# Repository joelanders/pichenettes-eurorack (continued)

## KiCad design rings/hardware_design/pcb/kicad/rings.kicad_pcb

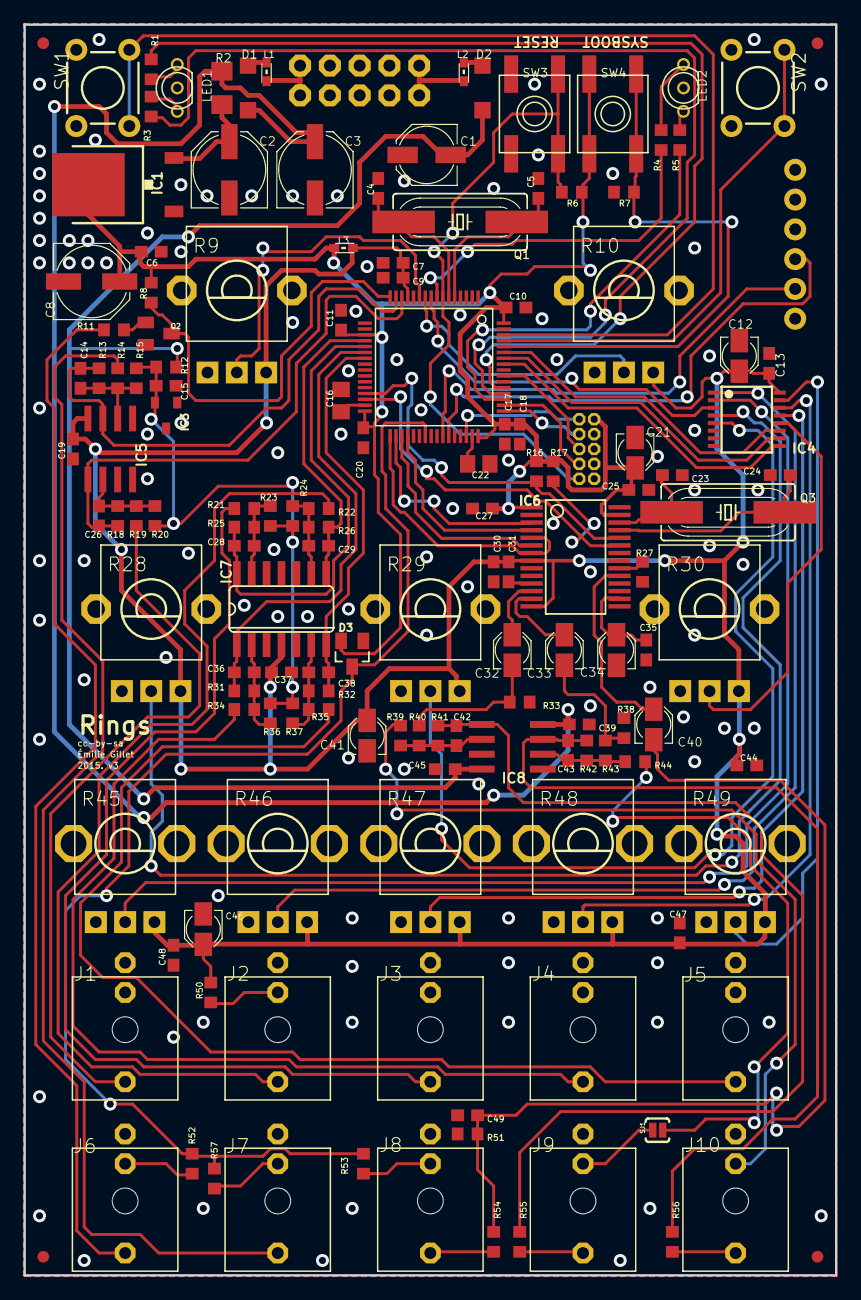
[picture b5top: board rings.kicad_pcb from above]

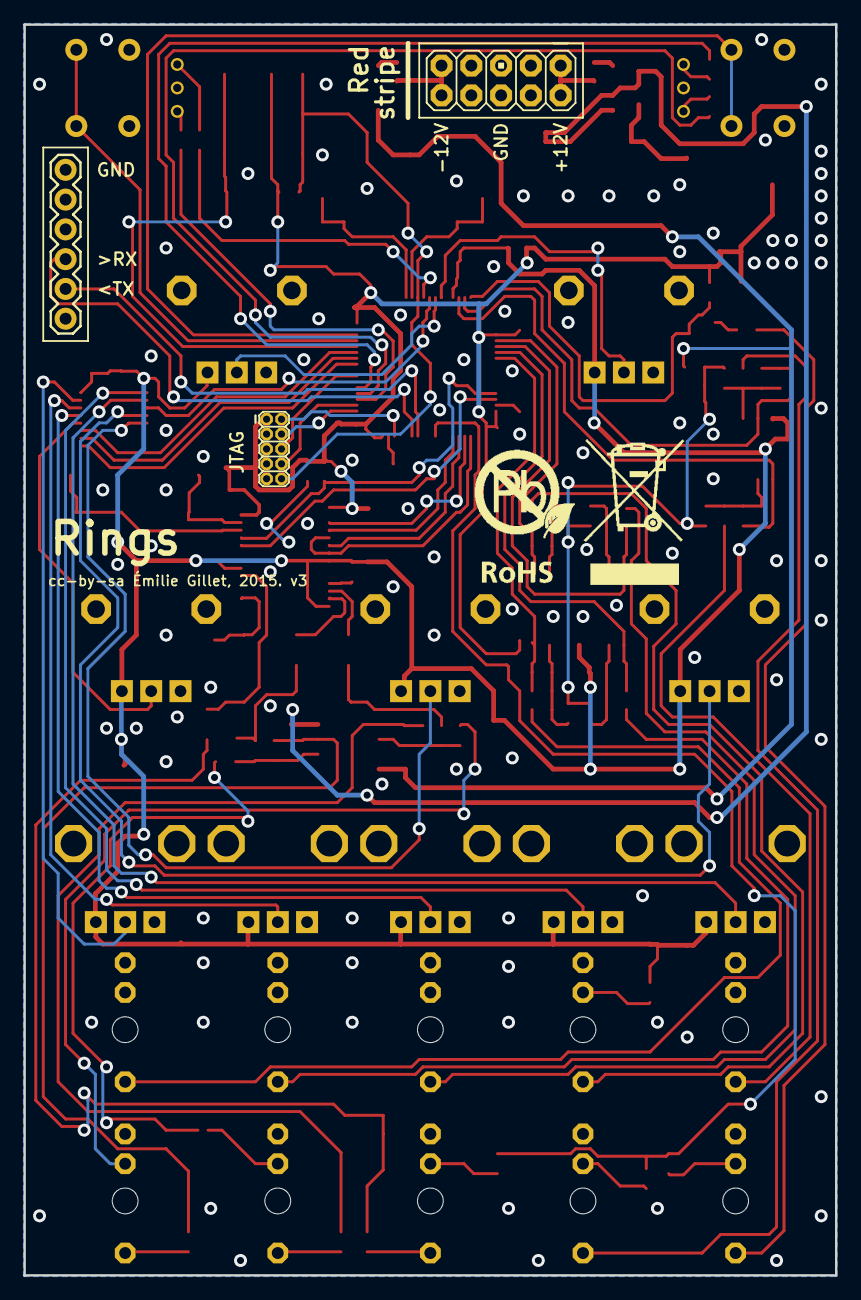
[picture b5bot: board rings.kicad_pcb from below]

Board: 2 copper layers, 69.2 x 106.7 mm, 148 parts (4 on the bottom side), 99 nets.

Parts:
C1: 22u; PANASONIC_C
C2, C3, C8: 47u; PANASONIC_D
C4, C5, C23, C24, C42, C43: 18p; C0603
C6, C9, C10, C11, C13, C15, C17, C19, C20, C25, C27, C31, C35, C37, C39, C44, C45, C47, C48: 100n; C0603
C7, C18, C30: 1u; C0603
C12, C21, C32, C33, C34, C40, C41, C46: 10u; PANASONIC_A
C14, C29: 2.2n; C0603
C16, C22: 2.2u; C0805
C26, C28, C36, C38: 10n; C0603
C49: 220p; C0603
D1, D2: 1N5819HW; SOD123
D3: BAT54S; SOT23
F1, F2, F3, F4: FIDUCIAL1X2; FIDUCIAL-1X2
IC1: LM1117-3.3; TO252
IC2: STM32F405RGT6; TQFP-10X10-64
IC3: LM4040B10; DBZ_R-PDSO-G3
IC4: 4051PW; TSSOP16
IC5: MCP6002; SO08
IC6: WM8731; SSOP28
IC7: MCP6004; SO14
IC8: TL072; SO08
J1, J2, J3, J4, J5, J6, J7, J8, J9, J10: PJ301_THONKICONN6; WQP_PJ_301M6
JP1: M05X2MINIJTAG; 2X5-1.27
JP2: 1X06
JP3: M05X2PTH; AVR_ICSP
L1, L2, L3: 0603
LED1, LED2: WP115VEGW; LED-BICOLOR-THROUGHHOLE
Q1: 8MHz; HC49UP
Q2: MMBT3904; SOT23-BEC
Q3: 12.288MHz; HC49UP
R1, R3, R4, R5: 180; R0603
R2: 4.7; R1206
R6, R7, R8: 10k; R0603
R9, R10, R28, R29, R30: 10kB; ALPS_POT_VERTICAL_PS
R11, R14, R19, R21, R22, R34, R35, R52: 100k; R0603
R12, R16, R17: 2.2k; R0603
R13, R33, R38, R39, R41, R42, R44: 47k; R0603
R15: 180k; R0603
R18, R25, R26, R31, R32: 20k; R0603
R20, R23, R24, R36, R37: 120k; R0603
R27, R54: 36k; R0603
R40, R43, R51: 6.8k; R0603
R45, R46, R47, R48, R49: 10kB; ALPS_POT_VERTICAL
R50: 3.3M; R0603
R53: 1M; R0603
R55, R56: 1.0k; R0603
R57: 470k; R0603
SJ1: SOLDERJUMPERNC2; SJ_2S-NOTRACE
SW1, SW2: TACTILE-PTH
SW3, SW4: EVQ-Q2
U$2: ROHS_BIG

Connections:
+3V3: C6.1, C8.+, C10.1, C11.1, C17.1, C18.1, C20.1, C21.+, C25.1, C27.1, D3.2, IC1.3, IC2.19, IC2.32, IC2.48, IC2.64, IC6.1, IC6.27, JP1.1, L3.1, R6.2, R8.2, R16.2, R17.2, SW4.B, SW4.B'
+3V3_A: C7.1, C9.1, C12.+, C13.1, C19.1, C30.1, C31.1, C37.1, C41.+, C44.1, C46.+, C47.1, C48.1, IC2.13, IC4.16, IC5.8, IC6.8, IC6.14, IC7.4, L3.2, R9.P$1, R10.P$1, R28.P$1, R29.P$1, R30.P$1, R45.P$1, R46.P$1, R47.P$1, R48.P$1, R49.P$1, R50.2
AREF_-10: C15.1, IC3.2, R12.2, R15.2, R20.2, R23.2, R24.2, R36.2, R37.2
AUX_OUT: C33.+, IC6.13
BOOT_FLASH: IC2.60, R7.2, SW4.A, SW4.A'
BRIGHTNESS_ATT: IC4.2, R45.P$2
BRIGHTNESS_CV: C26.2, IC2.14, IC5.1, R18.1
BRIGHTNESS_POT: IC4.4, R28.P$2
CV_NORMALIZATION: J7.P2, R57.2
DAMP_ATT: IC4.13, R47.P$2
DAMP_CV: C28.2, IC2.21, IC7.14, R25.1
DAMP_POT: IC4.5, R29.P$2
FM_CV: C29.2, IC2.20, IC7.8, R26.1
FREQUENCY_ATT: IC4.1, R46.P$2
FREQUENCY_POT: IC2.11, R9.P$2
GEOMETRY_ATT: IC4.14, R48.P$2
GEOMETRY_CV: C36.2, IC2.22, IC7.1, R31.1
GEOMETRY_POT: IC2.10, R10.P$2
GND: C1.+, C2.-, C3.-, C4.1, C5.1, C6.2, C7.2, C8.-, C9.2, C10.2, C11.2, C12.-, C13.2, C15.2, C16.2, C17.2, C18.2, C19.2, C20.2, C21.-, C22.2, C23.1, C24.1, C25.2, C27.2, C30.2, C31.2, C34.-, C35.2, C37.2, C39.2, C41.-, C44.2, C45.1, C46.-, C47.2, C48.2, C49.2, D3.1, IC1.1, IC2.12, IC2.18, IC2.26, IC2.28, IC2.63, IC3.1, IC4.6, IC4.7, IC4.8, IC5.3, IC5.4, IC5.5, IC6.11, IC6.15, IC6.21, IC6.22, IC6.28, IC7.3, IC7.5, IC7.10, IC7.11, IC7.12, IC8.3, IC8.5, J1.P1, J2.P1, J3.P1, J4.P1, J5.P1, J6.P1, J7.P1, J8.P1, J9.P1, J10.P1, JP1.3, JP1.5, JP1.9, JP2.1, JP3.3, JP3.4, JP3.5, JP3.6, JP3.7, JP3.8, LED1.2, LED2.2, Q2.E, R7.1, R9.P$3, R10.P$3, R27.2, R28.P$3, R29.P$3, R30.P$3, R33.1, R38.1, R45.P$3, R46.P$3, R47.P$3, R48.P$3, R49.P$3, R51.1, SW1.1, SW1.2, SW2.1, SW2.2, SW3.A, SW3.A'
I2C_SCL: IC2.29, IC6.24, R16.1
I2C_SDA: IC2.30, IC6.23, R17.1
I2S_LRCK: IC2.33, IC6.5, IC6.7
I2S_SCK: IC2.34, IC6.3
I2S_SIN: IC2.35, IC6.6
I2S_SOUT: IC2.36, IC6.4
IN_1: IC6.20, R27.1
IN_2: C40.+, IC6.19
JTCK: IC2.49, JP1.4
JTDI: IC2.50, JP1.8
JTDO: IC2.55, JP1.6
JTMS: IC2.46, JP1.2
MAIN_OUT: C32.+, IC6.12
MUXED_POTS: IC2.9, IC4.3
MUX_ADDR_0: IC2.59, IC4.11
MUX_ADDR_1: IC2.58, IC4.10
MUX_ADDR_2: IC2.57, IC4.9
unnamed: J1.P3, R19.2
unnamed: C26.1, IC5.2, R18.2, R19.1, R20.1
unnamed: J7.P3, R14.2
unnamed: J2.P3, R22.2
unnamed: C29.1, IC7.9, R22.1, R24.1, R26.2
unnamed: J4.P3, R34.2
unnamed: C5.2, IC2.5, Q1.2
unnamed: C4.2, IC2.6, Q1.1
unnamed: J6.P3, R11.1
unnamed: J3.P3, R21.2
unnamed: C28.1, IC7.13, R21.1, R23.1, R25.2
unnamed: LED1.3, R1.2
unnamed: C22.1, IC2.47
unnamed: C14.1, IC5.6, R13.2, R14.1, R15.1
unnamed: C36.1, IC7.2, R31.2, R34.1, R36.1
unnamed: C2.+, IC1.2, R2.1
unnamed: C34.+, C35.1, IC6.16
unnamed: C40.-, C49.1, R51.2, R54.1
unnamed: C16.1, IC2.31
unnamed: J6.P2, R52.2
unnamed: J8.P3, R54.2
unnamed: LED1.1, R3.2
unnamed: C33.-, R38.2, R43.2
unnamed: D1.A, L1.1
unnamed: C43.1, IC8.6, R42.2, R43.1, R44.1
unnamed: J5.P3, R35.2
unnamed: LED2.3, R4.2
unnamed: C43.2, IC8.7, R42.1, R56.2
unnamed: J10.P3, R56.1
unnamed: C38.1, IC7.6, R32.2, R35.1, R37.1
unnamed: C32.-, R33.2, R40.2
unnamed: C42.1, IC8.2, R39.1, R40.1, R41.2
unnamed: C42.2, IC8.1, R41.1, R55.2
unnamed: J9.P3, R55.1
unnamed: LED2.1, R5.2
unnamed: D2.C, L2.1
unnamed: IC2.52, R3.1
unnamed: J2.P2, R50.1
unnamed: J8.P2, R53.2
unnamed: IC2.8, R4.1
unnamed: C24.2, IC6.25, Q3.2
unnamed: C23.2, IC6.26, Q3.1
unnamed: IC2.53, R1.1
unnamed: IC2.51, R5.1
unnamed: J10.P2, R39.2
unnamed: R44.2, SJ1.1
unnamed: J9.P2, SJ1.2
unnamed: JP3.1, JP3.2, L1.2
unnamed: JP3.9, JP3.10, L2.2
unnamed: Q2.B, R11.2
NORMALIZATION_PROBE: D3.3, IC2.39, R52.1, R53.1, R57.1
POSITION_ATT: IC4.15, R49.P$2
POSITION_CV: C38.2, IC2.23, IC7.7, R32.1
POSITION_POT: IC4.12, R30.P$2
RESET: IC2.7, JP1.10, R6.1, SW3.B, SW3.B'
RX: IC2.43, JP2.4
STRUM: IC2.16, Q2.C, R8.1
SW_MODE: IC2.61, SW2.3, SW2.4
SW_POLYPHONY: IC2.62, SW1.3, SW1.4
TX: IC2.42, JP2.5
VCC: C3.+, C39.1, D1.C, IC8.8, R2.2
VEE: C1.-, C45.2, D2.A, IC8.4, R12.1
V_OCT_CV: C14.2, IC2.15, IC5.7, R13.1
